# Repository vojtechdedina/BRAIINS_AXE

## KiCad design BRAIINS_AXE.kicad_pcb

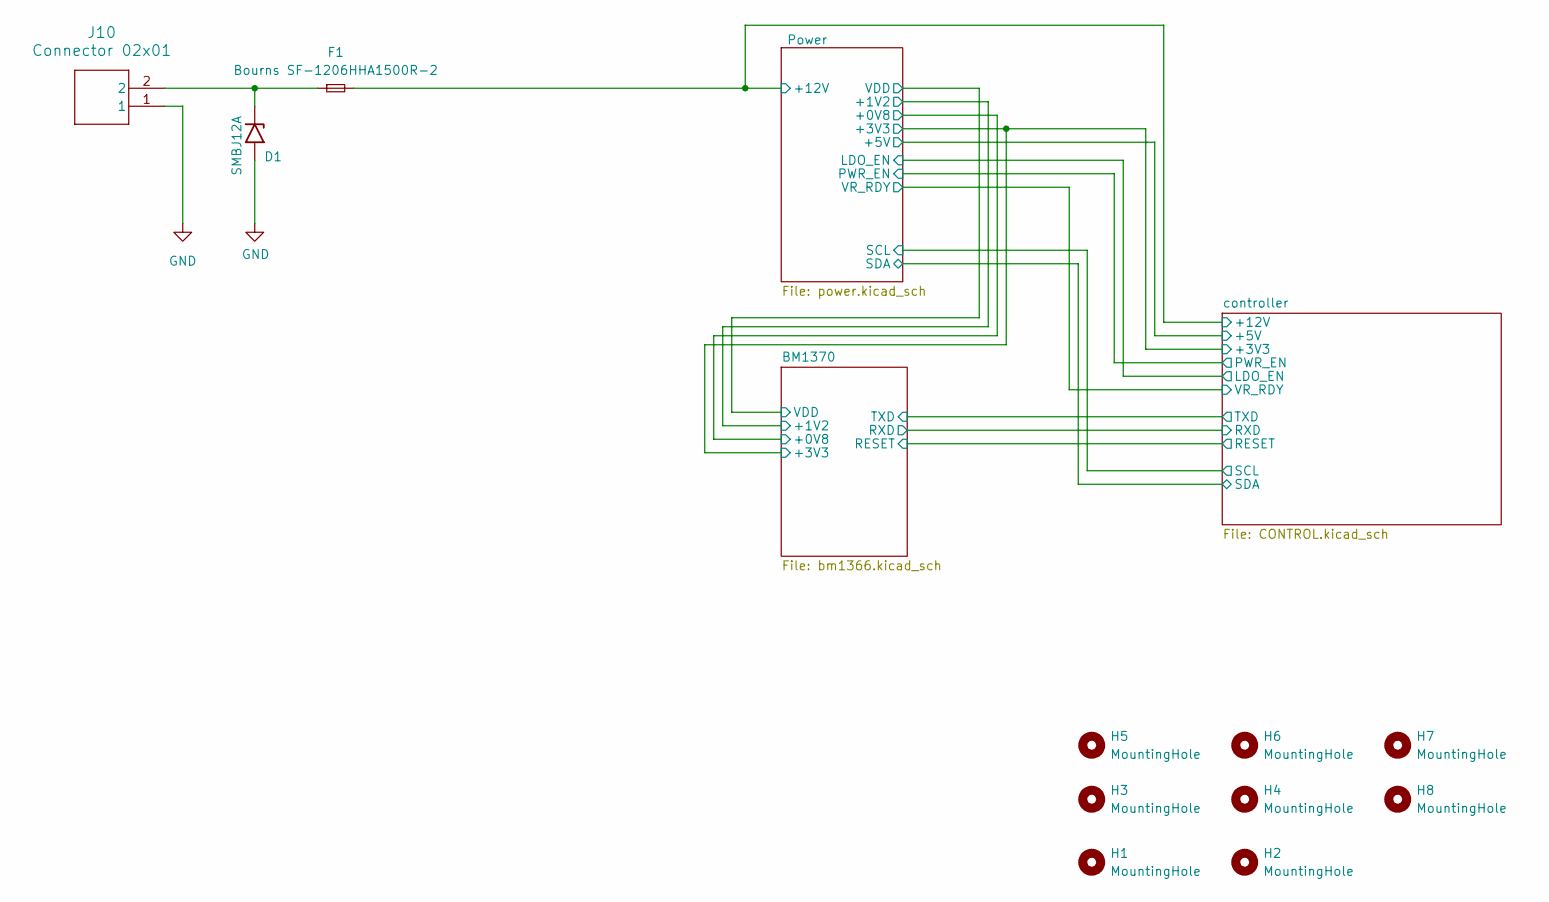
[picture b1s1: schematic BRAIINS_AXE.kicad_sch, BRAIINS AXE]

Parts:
D1: SMBJ12A; D_SMB
F1: Bourns SF-1206HHA1500R-2; Fuse_1210_3225Metric
H1, H2, H3, H4, H5, H6, H7, H8: MountingHole; MountingHole_3.2mm_M3_Pad_Via
J10: Connector 02x01; AMASS_XT60PW-M_1x02_P7.20mm_Horizontal

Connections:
+12V: F1.2; also elsewhere on the board
GND: D1.2 (A2), J10.1; also elsewhere on the board
unnamed: D1.1 (A1), F1.1, J10.2

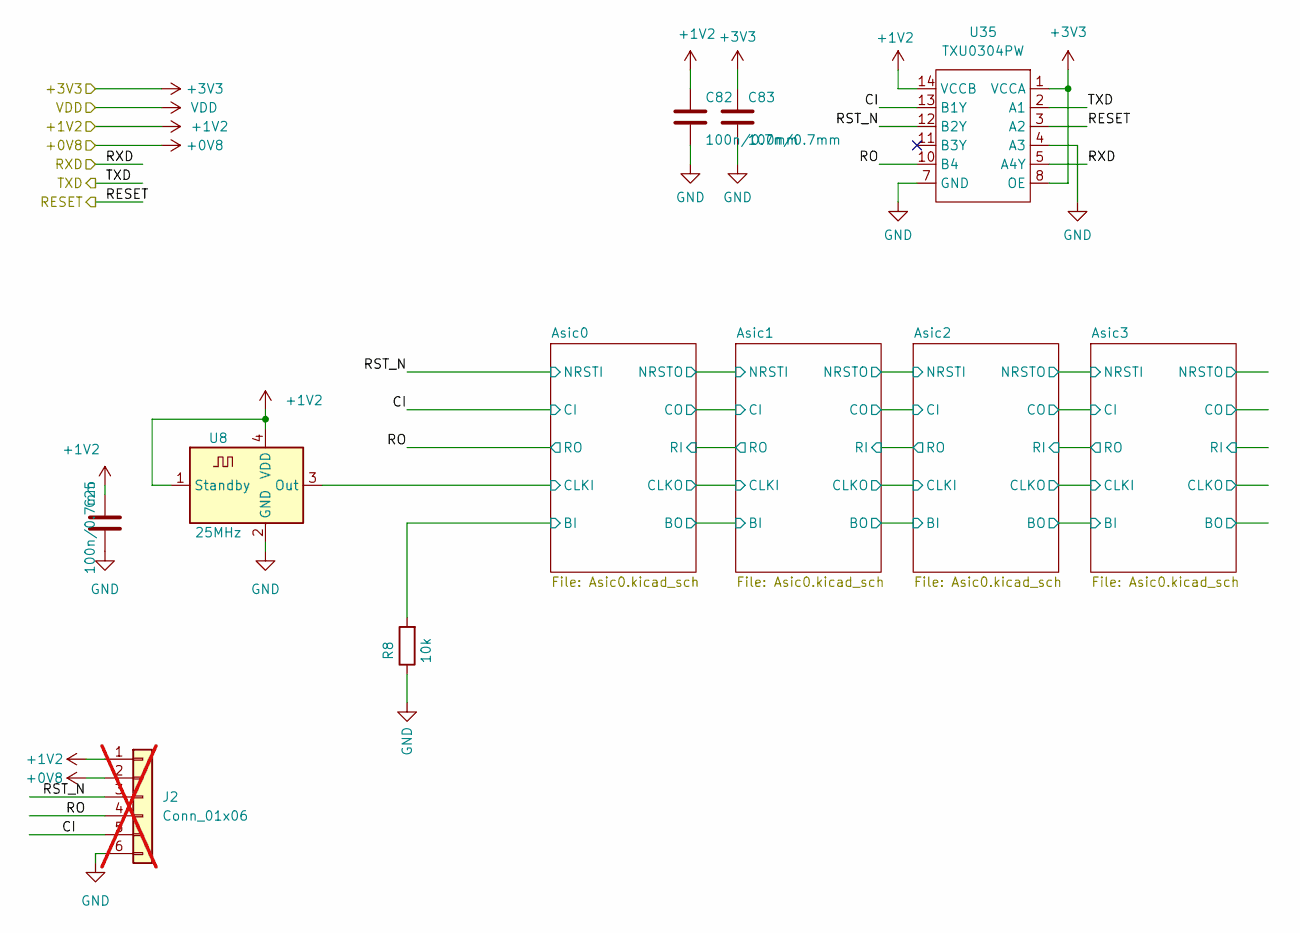
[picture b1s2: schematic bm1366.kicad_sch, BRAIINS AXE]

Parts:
C25, C82, C83: 100n/0.7mm; C_0805_2012Metric
J2: Conn_01x06; PinHeader_1x06_P1.27mm_Vertical; not fitted
R8: 10k; R_0805_2012Metric
U8: 25MHz; Oscillator_SMD_EuroQuartz_XO32-4Pin_3.2x2.5mm
U35: TXU0304PW; TSSOP-14-1EP_4.4x5mm_P0.65mm

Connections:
+0V8: J2.2; also elsewhere on the board
+1V2: C25.1, C82.1, J2.1, U8.1 (Standby), U8.4 (VDD), U35.14 (VCCB); also elsewhere on the board
+3V3: C83.1, U35.1 (VCCA), U35.8 (OE); also elsewhere on the board
/BM1370/Asic0/BI: R8.2; also elsewhere on the board
/BM1370/Asic0/CLKI: U8.3 (Out); also elsewhere on the board
/BM1370/CI: J2.5, U35.13 (B1Y); also elsewhere on the board
/BM1370/RESET: U35.3 (A2); also elsewhere on the board
/BM1370/RO: J2.4, U35.10 (B4); also elsewhere on the board
/BM1370/RST_N: J2.3, U35.12 (B2Y); also elsewhere on the board
/BM1370/RXD: U35.5 (A4Y); also elsewhere on the board
/BM1370/TXD: U35.2 (A1); also elsewhere on the board
GND: C25.2, C82.2, C83.2, J2.6, R8.1, U8.2 (GND), U35.4 (A3), U35.7 (GND); also elsewhere on the board

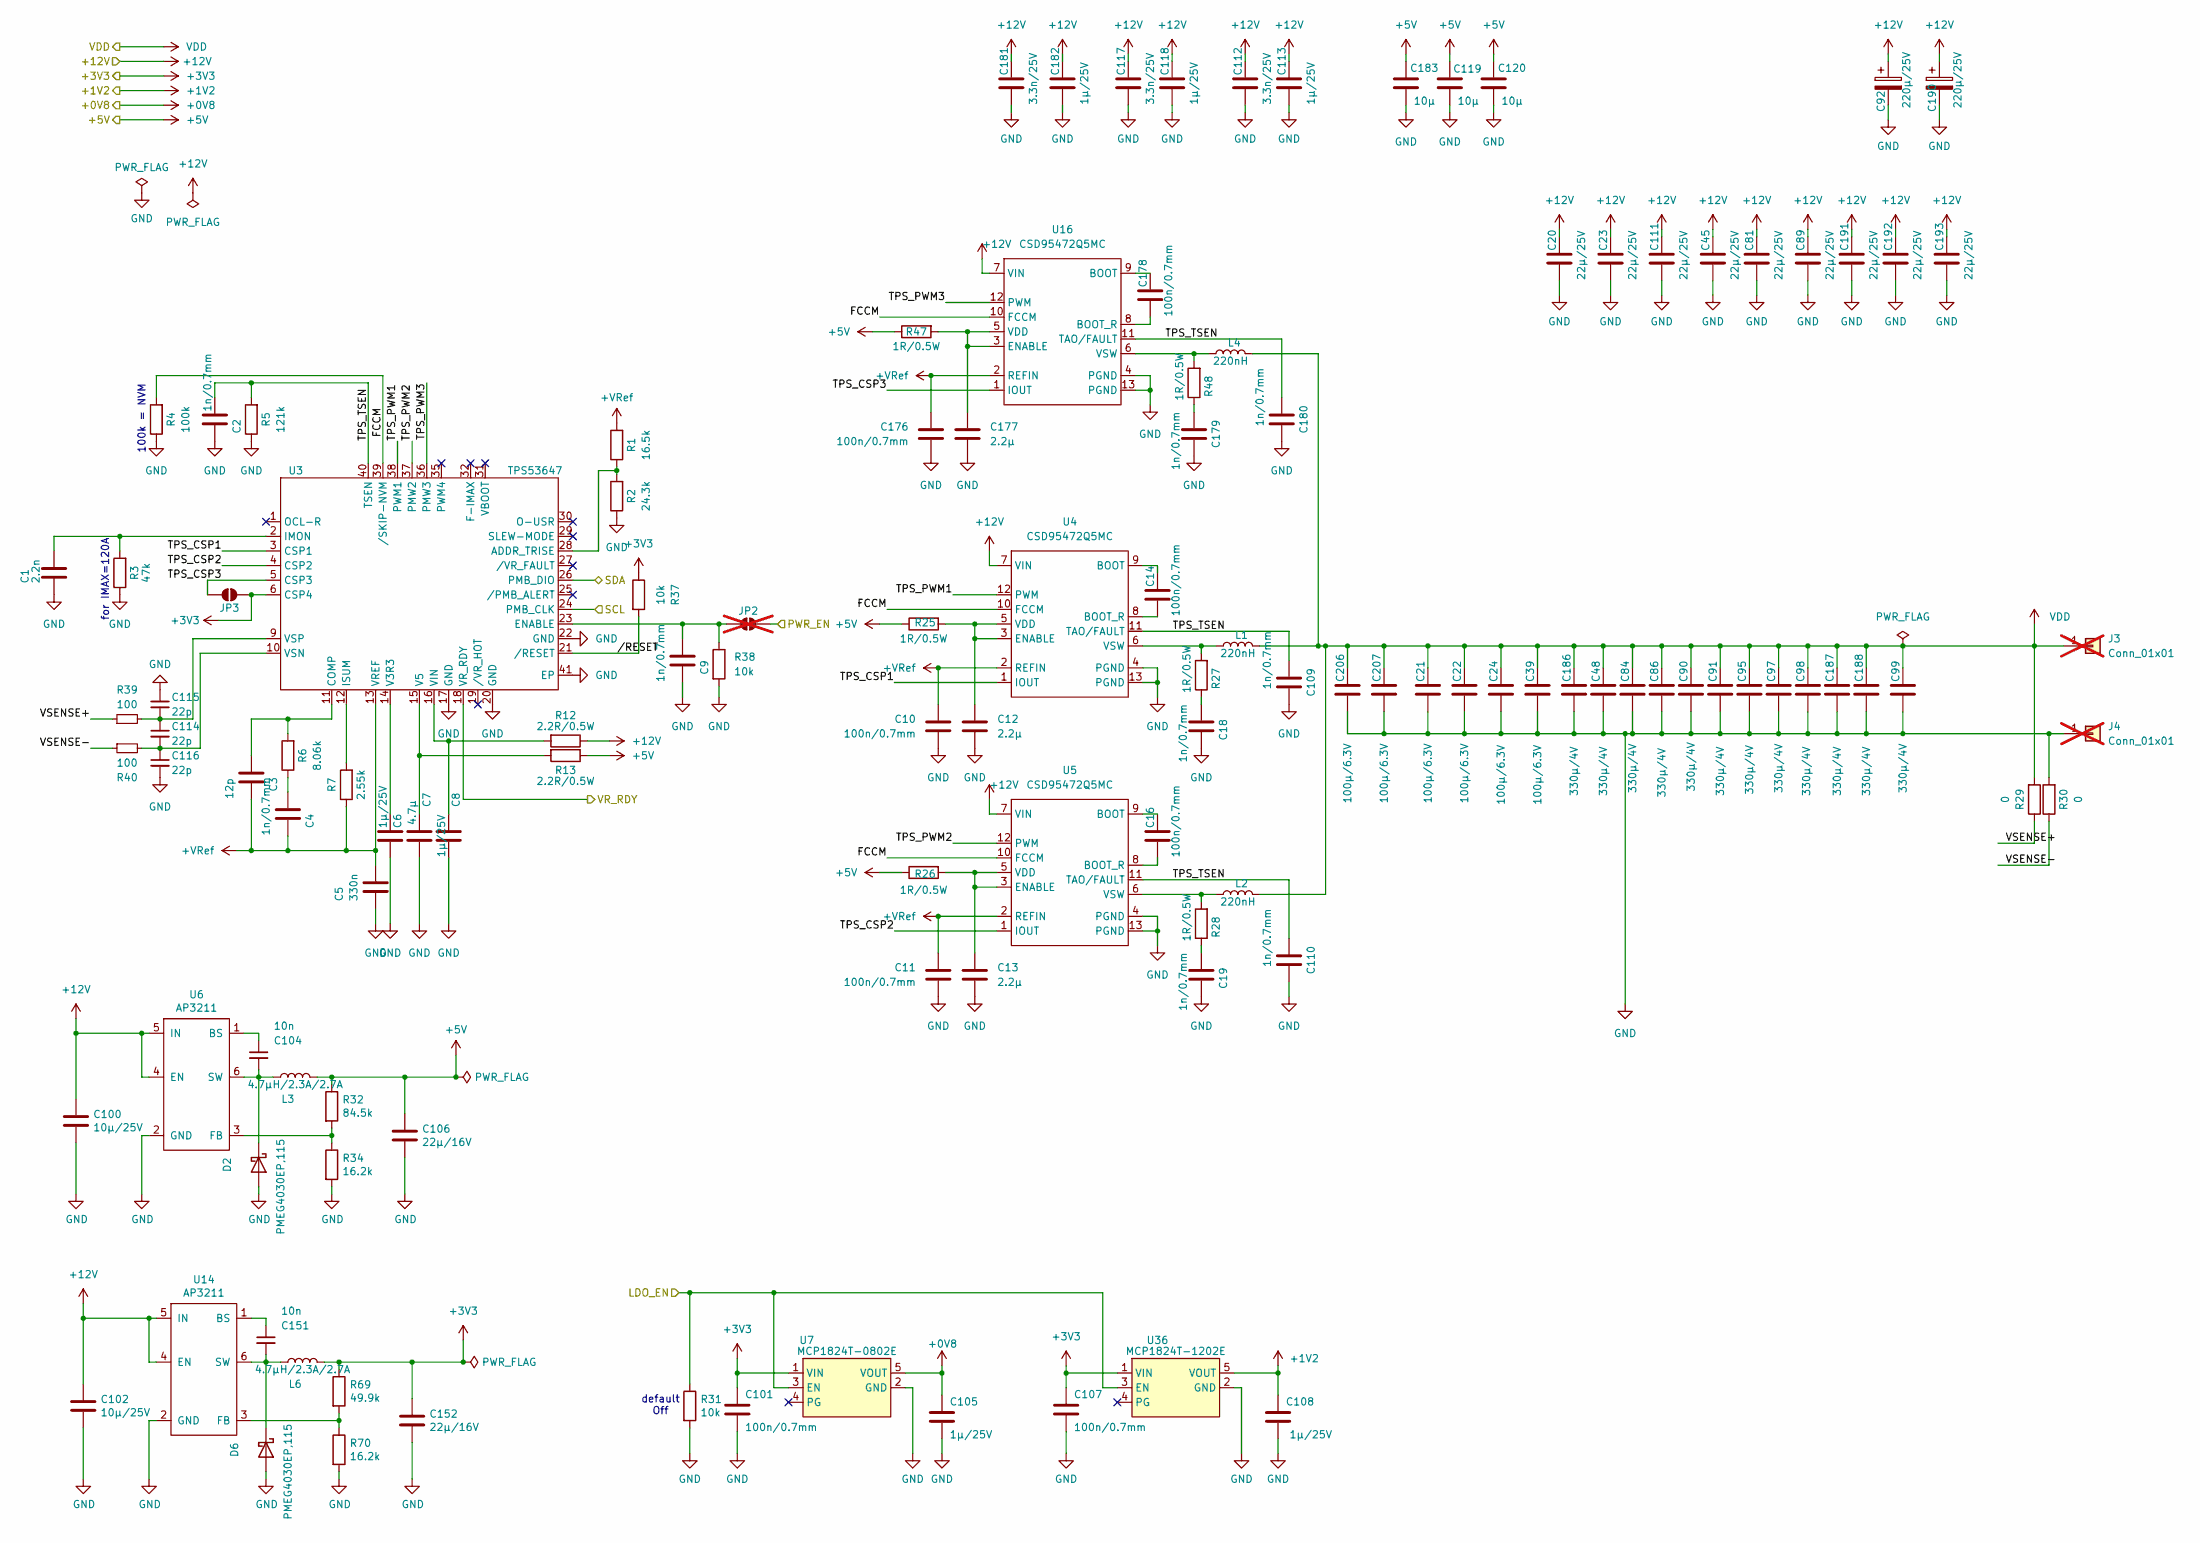
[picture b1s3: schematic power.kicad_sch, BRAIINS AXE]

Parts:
C1: 2.2n; C_0603_1608Metric
C2, C4, C9: 1n/0.7mm; C_0603_1608Metric
C3: 12p; C_0603_1608Metric
C5: 330n; C_0603_1608Metric
C6, C8, C113, C118, C182: 1µ/25V; C_0603_1608Metric
C7: 4.7µ; C_0603_1608Metric
C10, C11, C14, C16, C176, C178: 100n/0.7mm; C_0603_1608Metric
C12, C13, C177: 2.2µ; C_0603_1608Metric
C18, C19, C109, C110, C179, C180: 1n/0.7mm; C_0805_2012Metric
C20, C23, C45, C81, C89, C111, C191, C192, C193: 22µ/25V; C_1210_3225Metric
C21, C22, C24, C39, C206, C207: 100µ/6.3V; C_1210_3225Metric
C48, C84, C86, C90, C91, C95, C97, C98, C99, C186, C187, C188: 330µ/4V; C_1210_3225Metric
C92, C190: 220µ/25V; CP_Elec_8x10
C100, C102: 10µ/25V; C_0805_2012Metric
C101, C107: 100n/0.7mm; C_0805_2012Metric
C104, C151: 10n; C_0805_2012Metric
C105, C108: 1µ/25V; C_0805_2012Metric
C106, C152: 22µ/16V; C_1206_3216Metric
C112, C117, C181: 3.3n/25V; C_0603_1608Metric
C114, C115, C116: 22p; C_0603_1608Metric
C119, C120, C183: 10µ; C_0805_2012Metric
D2, D6: PMEG4030EP,115; D_SOD-128
J3, J4: Conn_01x01; Wuerth_REDCUBE-THR_WP-THRBU_74650194_THR; not fitted
JP2: SolderJumper_2_Open; SolderJumper-2_P1.3mm_Open_RoundedPad1.0x1.5mm; not fitted
JP3: SolderJumper_2_Open; SolderJumper-2_P1.3mm_Open_RoundedPad1.0x1.5mm
L1, L2, L4: 220nH; IFLR-4031GC-01-8x10
L3, L6: 4.7µH/2.3A/2.7A; L_Taiyo-Yuden_NR-50xx
R1: 16.5k; R_0603_1608Metric
R2: 24.3k; R_0603_1608Metric
R3: 47k; R_0603_1608Metric
R4: 100k; R_0603_1608Metric
R5: 121k; R_0603_1608Metric
R6: 8.06k; R_0603_1608Metric
R7: 2.55k; R_0603_1608Metric
R12, R13: 2.2R/0.5W; R_0805_2012Metric
R25, R26, R27, R28, R47, R48: 1R/0.5W; R_0805_2012Metric
R29, R30: 0; R_0805_2012Metric
R31: 10k; R_0805_2012Metric
R32: 84.5k; R_0603_1608Metric
R34, R70: 16.2k; R_0603_1608Metric
R37, R38: 10k; R_0603_1608Metric
R39, R40: 100; R_0603_1608Metric
R69: 49.9k; R_0603_1608Metric
U3: TPS53647; Texas_RHA0040B_VQFN-40-1EP_6x6mm_P0.5mm_EP4.15x4.15mm_Therm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
U4, U5, U16: CSD95472Q5MC; CSD95472-SON-5x6
U6, U14: AP3211; SOT-23-6
U7: MCP1824T-0802E; SOT-23-5
U36: MCP1824T-1202E; SOT-23-5

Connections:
+0V8: C105.1, U7.5 (VOUT); also elsewhere on the board
+1V2: C108.1, U36.5 (VOUT); also elsewhere on the board
+3V3: C101.1, C107.1, C152.1, JP3.2 (B), L6.2, R37.1, R69.1, U3.6 (CSP4), U7.1 (VIN), U36.1 (VIN); also elsewhere on the board
+5V: C106.1, C119.1, C120.1, C183.1, L3.2, R13.1, R25.1, R26.1, R32.1, R47.1
+12V: C20.1, C23.1, C45.1, C81.1, C89.1, C92.1, C100.1, C102.1, C111.1, C112.1, C113.1, C117.1, C118.1, C181.1, C182.1, C190.1, C191.1, C192.1, C193.1, R12.1, U4.7 (VIN), U5.7 (VIN), U6.4 (EN), U6.5 (IN), U14.4 (EN), U14.5 (IN), U16.7 (VIN); also elsewhere on the board
+VRef: C3.2, C4.2, C5.1, C10.1, C11.1, C176.1, R1.2, R7.1, U3.13 (VREF), U4.2 (REFIN), U5.2 (REFIN), U16.2 (REFIN)
/Power/FCCM: R4.2, U3.39 (/SKIP-NVM), U4.10 (FCCM), U5.10 (FCCM), U16.10 (FCCM)
/Power/LDO_EN: R31.1, U7.3 (EN), U36.3 (EN); also elsewhere on the board
/Power/PWR_EN: JP2.2 (B); also elsewhere on the board
/Power/TPS_CSP1: U3.3 (CSP1), U4.1 (IOUT)
/Power/TPS_CSP2: U3.4 (CSP2), U5.1 (IOUT)
/Power/TPS_CSP3: JP3.1 (A), U3.5 (CSP3), U16.1 (IOUT)
/Power/TPS_PWM1: U3.38 (PWM1), U4.12 (PWM)
/Power/TPS_PWM2: U3.37 (PMW2), U5.12 (PWM)
/Power/TPS_PWM3: U3.36 (PMW3), U16.12 (PWM)
/Power/TPS_TSEN: C2.1, C109.1, C110.1, C180.1, R5.2, U3.40 (TSEN), U4.11 (TAO/FAULT), U5.11 (TAO/FAULT), U16.11 (TAO/FAULT)
/Power/VR_RDY: U3.18 (VR_RDY); also elsewhere on the board
/Power/VSENSE+: R29.1, R39.1
/Power/VSENSE-: R30.1, R40.1
/Power//RESET: R37.2, U3.21 (/RESET)
/controller/SCL: U3.24 (PMB_CLK); also elsewhere on the board
/controller/SDA: U3.26 (PMB_DIO); also elsewhere on the board
GND: C1.2, C2.2, C5.2, C6.2, C7.1, C8.1, C9.2, C10.2, C11.2, C12.2, C13.2, C18.2, C19.2, C20.2, C21.2, C22.2, C23.2, C24.2, C39.2, C45.2, C48.2, C81.2, C84.2, C86.2, C89.2, C90.2, C91.2, C92.2, C95.2, C97.2, C98.2, C99.2, C100.2, C101.2, C102.2, C105.2, C106.2, C107.2, C108.2, C109.2, C110.2, C111.2, C112.2, C113.2, C115.1, C116.2, C117.2, C118.2, C119.2, C120.2, C152.2, C176.2, C177.2, C179.2, C180.2, C181.2, C182.2, C183.2, C186.2, C187.2, C188.2, C190.2, C191.2, C192.2, C193.2, C206.2, C207.2, D2.2 (A), D6.2 (A), J4.1, R2.1, R3.1, R4.1, R5.1, R30.2, R31.2, R34.2, R38.2, R70.2, U3.17 (GND), U3.20 (GND), U3.22 (GND), U3.41 (EP), U4.4 (PGND), U4.13 (PGND), U5.4 (PGND), U5.13 (PGND), U6.2 (GND), U7.2 (GND), U14.2 (GND), U16.4 (PGND), U16.13 (PGND), U36.2 (GND); also elsewhere on the board
unnamed: C4.1, R6.1
unnamed: C18.1, R27.1
unnamed: C19.1, R28.1
unnamed: C179.1, R48.1
unnamed: C104.2, D2.1 (K), L3.1, U6.6 (SW)
unnamed: C151.2, D6.1 (K), L6.1, U14.6 (SW)
unnamed: C9.1, JP2.1 (A), R38.1, U3.23 (ENABLE)
unnamed: R1.1, R2.2, U3.28 (ADDR_TRISE)
unnamed: C3.1, R6.2, U3.11 (COMP)
unnamed: C1.1, R3.2, U3.2 (IMON)
unnamed: R7.2, U3.12 (ISUM)
unnamed: C6.1, U3.14 (V3R3)
unnamed: C7.2, R13.2, U3.15 (V5)
unnamed: C8.2, R12.2, U3.16 (VIN)
unnamed: C114.2, C116.1, R40.2, U3.10 (VSN)
unnamed: C114.1, C115.2, R39.2, U3.9 (VSP)
unnamed: C14.1, U4.9 (BOOT)
unnamed: C14.2, U4.8 (BOOT_R)
unnamed: C12.1, R25.2, U4.3 (ENABLE), U4.5 (VDD)
unnamed: L1.1, R27.2, U4.6 (VSW)
unnamed: C16.1, U5.9 (BOOT)
unnamed: C16.2, U5.8 (BOOT_R)
unnamed: C13.1, R26.2, U5.3 (ENABLE), U5.5 (VDD)
unnamed: L2.1, R28.2, U5.6 (VSW)
unnamed: C104.1, U6.1 (BS)
unnamed: R32.2, R34.1, U6.3 (FB)
unnamed: C151.1, U14.1 (BS)
unnamed: R69.2, R70.1, U14.3 (FB)
unnamed: C178.1, U16.9 (BOOT)
unnamed: C178.2, U16.8 (BOOT_R)
unnamed: C177.1, R47.2, U16.3 (ENABLE), U16.5 (VDD)
unnamed: L4.1, R48.2, U16.6 (VSW)
VDD: C21.1, C22.1, C24.1, C39.1, C48.1, C84.1, C86.1, C90.1, C91.1, C95.1, C97.1, C98.1, C99.1, C186.1, C187.1, C188.1, C206.1, C207.1, J3.1, L1.2, L2.2, L4.2, R29.2; also elsewhere on the board

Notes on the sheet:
default Off
for IMAX=120A
100k = NVM

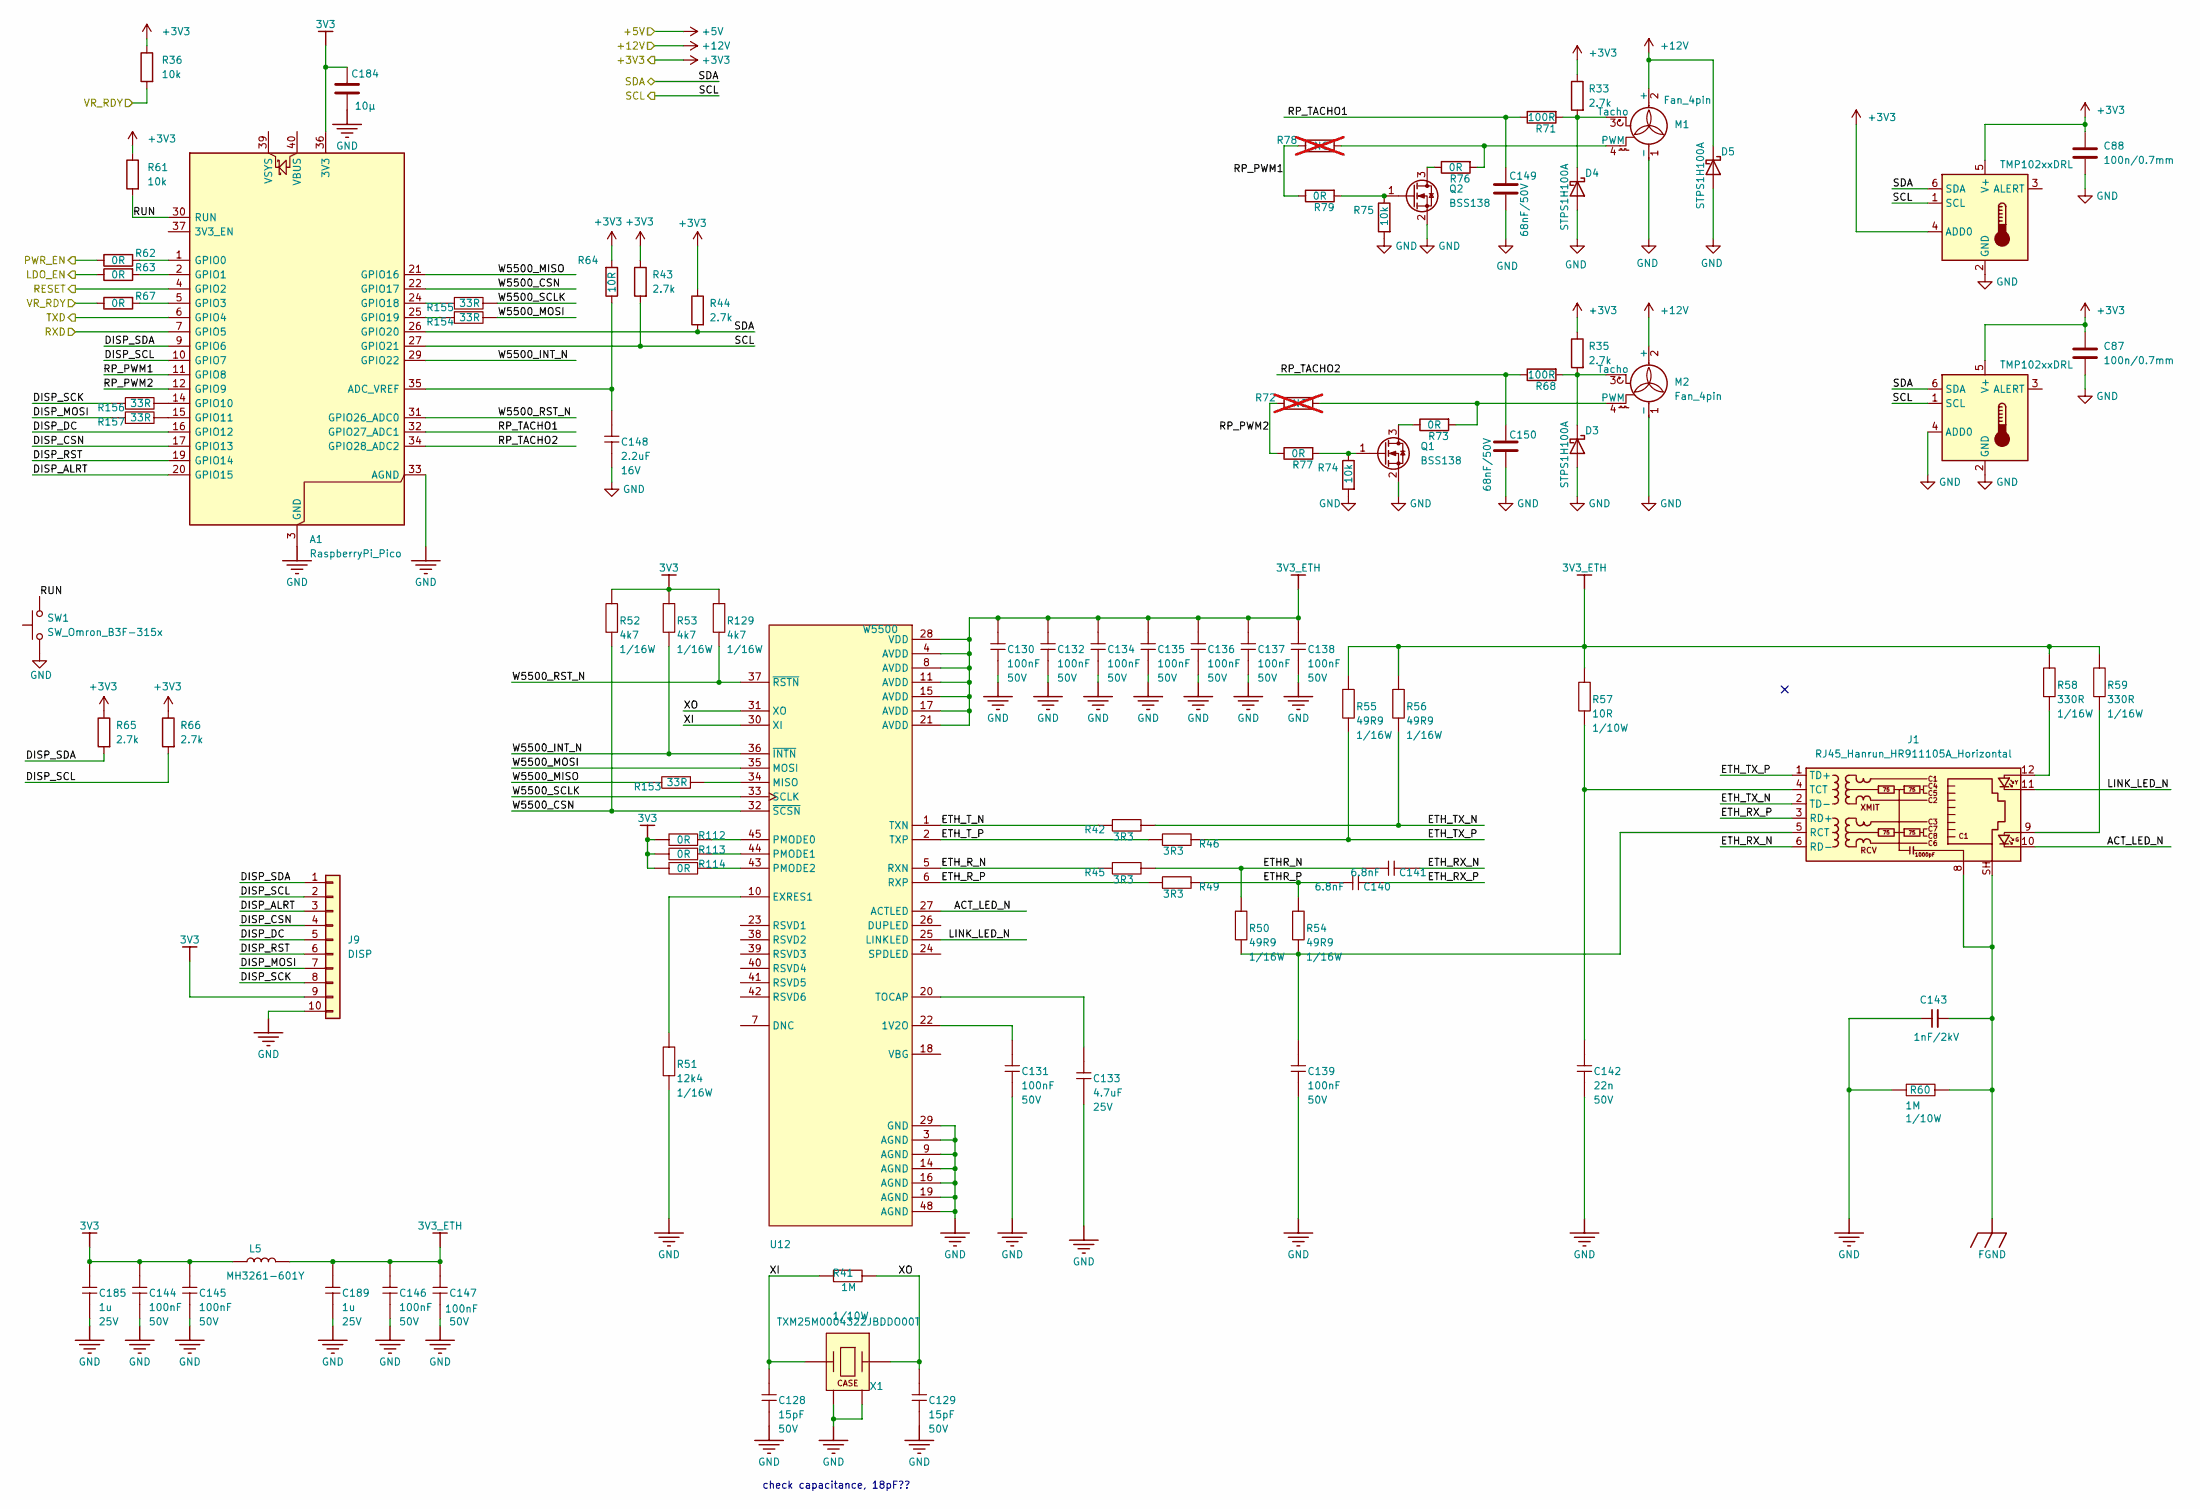
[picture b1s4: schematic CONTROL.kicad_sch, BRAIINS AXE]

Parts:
A1: RaspberryPi_Pico; RaspberryPi_Pico_Common_Unspecified
C87, C88: 100n/0.7mm; C_0603_1608Metric
C128, C129: 15pF; C_0603_1608Metric; VOLTAGE_RATING 50V; TOLERANCE 1%; PART_TYPE Capacitor
C130, C131, C132, C134, C135, C136, C137, C138, C139, C144, C145, C146, C147: 100nF; C_0603_1608Metric; VOLTAGE_RATING 50V; TOLERANCE 10%; PART_TYPE Capacitor
C133: 4.7uF; C_0603_1608Metric; VOLTAGE_RATING 25V; TOLERANCE 10%; PART_TYPE Capacitor
C140, C141: 6.8nF; C_0603_1608Metric; VOLTAGE_RATING 50V; TOLERANCE 10%; PART_TYPE Capacitor
C142: 22n; C_0603_1608Metric; VOLTAGE_RATING 50V; TOLERANCE 10%; PART_TYPE Capacitor
C143: 1nF/2kV; C_1206_3216Metric
C148: 2.2uF; C_0603_1608Metric; VOLTAGE_RATING 16V; TOLERANCE 10%; PART_TYPE Capacitor
C149, C150: 68nF/50V; C_0603_1608Metric
C184: 10µ; C_0805_2012Metric
C185, C189: 1u; C_0603_1608Metric; VOLTAGE_RATING 25V; TOLERANCE 10%; PART_TYPE Capacitor
D3, D4, D5: STPS1H100A; D_SMA
J1: RJ45_Hanrun_HR911105A_Horizontal
J9: DISP; PinHeader_1x10_P2.54mm_Vertical
L5: MH3261-601Y; L_1206_3216Metric; PART_TYPE Filter
M1, M2: Fan_4pin; FanPinHeader_1x04_P2.54mm_Vertical
Q1, Q2: BSS138; SOT-23
R33, R35, R43, R44, R65, R66: 2.7k; R_0603_1608Metric
R36, R61, R74, R75: 10k; R_0603_1608Metric
R41, R60: 1M; R_0603_1608Metric; TOLERANCE 1%; PART_TYPE Resistor
R42, R45, R46, R49: 3R3; R_0603_1608Metric; TOLERANCE 1%; PART_TYPE Resistor
R50, R54, R55, R56: 49R9; R_0603_1608Metric; TOLERANCE 1%; PART_TYPE Resistor
R51: 12k4; R_0603_1608Metric; TOLERANCE 1%; PART_TYPE Resistor
R52, R53, R129: 4k7; R_0603_1608Metric; TOLERANCE 1%; PART_TYPE Resistor
R57: 10R; R_0603_1608Metric; TOLERANCE 1%; PART_TYPE Resistor
R58, R59: 330R; R_0603_1608Metric; TOLERANCE 1%; PART_TYPE Resistor
R62, R63, R67, R73, R76, R77, R79: 0R; R_0603_1608Metric
R64: 10R; R_0603_1608Metric
R68, R71: 100R; R_0603_1608Metric
R72, R78: NC; R_0603_1608Metric; not fitted
R112, R113, R114: 0R; R_0603_1608Metric; TOLERANCE 1%; PART_TYPE Resistor
R153, R154, R155, R156, R157: 33R; R_0603_1608Metric; TOLERANCE 1%; PART_TYPE Resistor
SW1: SW_Omron_B3F-315x; SW_SPST_Omron_B3F-315x_Angled
U1, U13: TMP102xxDRL; SOT-563
U12: W5500; LQFP-48_7x7mm_P0.5mm; PART_TYPE IC; LCSC C32843
X1: TXM25M0004322JBDDO00T; Crystal_SMD_3225-4Pin_3.2x2.5mm; PART_TYPE Crystal; LCSC C362473

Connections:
3V3: A1.36 (3V3), C144.1, C145.1, C184.1, C185.1, J9.9, L5.1, R52.2, R53.2, R112.2, R113.2, R114.2, R129.2
3V3_ETH: C130.1, C132.1, C134.1, C135.1, C136.1, C137.1, C138.1, C146.1, C147.1, C189.1, L5.2, R55.2, R56.2, R57.2, R58.2, R59.2, U12.4 (AVDD), U12.8 (AVDD), U12.11 (AVDD), U12.15 (AVDD), U12.17 (AVDD), U12.21 (AVDD), U12.28 (VDD)
+3V3: C87.1, C88.1, R33.1, R35.1, R36.1, R43.1, R44.1, R61.1, R64.2, R65.1, R66.1, U1.5 (V+), U13.4 (ADD0), U13.5 (V+); also elsewhere on the board
+12V: D5.1 (K), M1.2 (+), M2.2 (+); also elsewhere on the board
/BM1370/RESET: A1.4 (GPIO2); also elsewhere on the board
/BM1370/RXD: A1.7 (GPIO5); also elsewhere on the board
/BM1370/TXD: A1.6 (GPIO4); also elsewhere on the board
/Power/LDO_EN: R63.1; also elsewhere on the board
/Power/PWR_EN: R62.1; also elsewhere on the board
/Power/VR_RDY: R36.2, R67.1; also elsewhere on the board
/controller/ACT_LED_N: J1.10, U12.27 (ACTLED)
/controller/DISP_ALRT: A1.20 (GPIO15), J9.3
/controller/DISP_CSN: A1.17 (GPIO13), J9.4
/controller/DISP_DC: A1.16 (GPIO12), J9.5
/controller/DISP_MOSI: J9.7, R157.1
/controller/DISP_RST: A1.19 (GPIO14), J9.6
/controller/DISP_SCK: J9.8, R156.1
/controller/DISP_SCL: A1.10 (GPIO7), J9.2, R66.2
/controller/DISP_SDA: A1.9 (GPIO6), J9.1, R65.2
/controller/ETHR_N: C141.1, R45.2, R50.2
/controller/ETHR_P: C140.1, R49.2, R54.2
/controller/ETH_RX_N: C141.2, J1.6 (RD-)
/controller/ETH_RX_P: C140.2, J1.3 (RD+)
/controller/ETH_R_N: R45.1, U12.5 (RXN)
/controller/ETH_R_P: R49.1, U12.6 (RXP)
/controller/ETH_TX_N: J1.2 (TD-), R42.2, R56.1
/controller/ETH_TX_P: J1.1 (TD+), R46.2, R55.1
/controller/ETH_T_N: R42.1, U12.1 (TXN)
/controller/ETH_T_P: R46.1, U12.2 (TXP)
/controller/LINK_LED_N: J1.11, U12.25 (LINKLED)
/controller/RP_PWM1: A1.11 (GPIO8), R78.1, R79.1
/controller/RP_PWM2: A1.12 (GPIO9), R72.1, R77.1
/controller/RP_TACHO1: A1.32 (GPIO27_ADC1), C149.1, R71.1
/controller/RP_TACHO2: A1.34 (GPIO28_ADC2), C150.1, R68.1
/controller/RUN: A1.30 (RUN), R61.2, SW1.2
/controller/SCL: A1.27 (GPIO21), R43.2, U1.1 (SCL), U13.1 (SCL); also elsewhere on the board
/controller/SDA: A1.26 (GPIO20), R44.2, U1.6 (SDA), U13.6 (SDA); also elsewhere on the board
/controller/W5500_CSN: A1.22 (GPIO17), R52.1, U12.32 (~SCSN)
/controller/W5500_INT_N: A1.29 (GPIO22), R53.1, U12.36 (~INTN)
/controller/W5500_MISO: A1.21 (GPIO16), R153.1
/controller/W5500_MOSI: R154.2, U12.35 (MOSI)
/controller/W5500_RST_N: A1.31 (GPIO26_ADC0), R129.1, U12.37 (~RSTN)
/controller/W5500_SCLK: R155.2, U12.33 (SCLK)
/controller/XI: C128.1, R41.1, U12.30 (XI), X1.1 (X1)
/controller/XO: C129.1, R41.2, U12.31 (XO), X1.3 (X2)
FGND: C143.2, J1.8, J1.SH, R60.2
GND: A1.3 (GND), A1.8 (GND), A1.13 (GND), A1.18 (GND), A1.23 (GND), A1.28 (GND), A1.33 (AGND), A1.38 (GND), C87.2, C88.2, C128.2, C129.2, C130.2, C131.2, C132.2, C133.2, C134.2, C135.2, C136.2, C137.2, C138.2, C139.2, C142.2, C143.1, C144.2, C145.2, C146.2, C147.2, C148.2, C149.2, C150.2, C184.2, C185.2, C189.2, D3.2 (A), D4.2 (A), D5.2 (A), J9.10, M1.1 (-), M2.1 (-), Q1.2 (S), Q2.2 (S), R51.1, R60.1, R74.2, R75.2, SW1.1, U1.2 (GND), U1.4 (ADD0), U12.3 (AGND), U12.9 (AGND), U12.14 (AGND), U12.16 (AGND), U12.19 (AGND), U12.29 (GND), U12.48 (AGND), U13.2 (GND), X1.2 (CASE), X1.4 (CASE); also elsewhere on the board
unnamed: A1.35 (ADC_VREF), C148.1, R64.1
unnamed: A1.1 (GPIO0), R62.2
unnamed: A1.2 (GPIO1), R63.2
unnamed: A1.5 (GPIO3), R67.2
unnamed: A1.14 (GPIO10), R156.2
unnamed: A1.15 (GPIO11), R157.2
unnamed: A1.24 (GPIO18), R155.1
unnamed: A1.25 (GPIO19), R154.1
unnamed: D3.1 (K), M2.3 (Tacho), R35.2, R68.2
unnamed: D4.1 (K), M1.3 (Tacho), R33.2, R71.2
unnamed: J1.9, R59.1
unnamed: J1.12, R58.1
unnamed: C139.1, J1.5 (RCT), R50.1, R54.1
unnamed: C142.1, J1.4 (TCT), R57.1
unnamed: M1.4 (PWM), R76.2, R78.2
unnamed: M2.4 (PWM), R72.2, R73.2
unnamed: Q1.3 (D), R73.1
unnamed: Q1.1 (G), R74.1, R77.2
unnamed: Q2.3 (D), R76.1
unnamed: Q2.1 (G), R75.1, R79.2
unnamed: C131.1, U12.22 (1V2O)
unnamed: R51.2, U12.10 (EXRES1)
unnamed: R153.2, U12.34 (MISO)
unnamed: R112.1, U12.45 (PMODE0)
unnamed: R113.1, U12.44 (PMODE1)
unnamed: R114.1, U12.43 (PMODE2)
unnamed: C133.1, U12.20 (TOCAP)

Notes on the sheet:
check capacitance, 18pF??

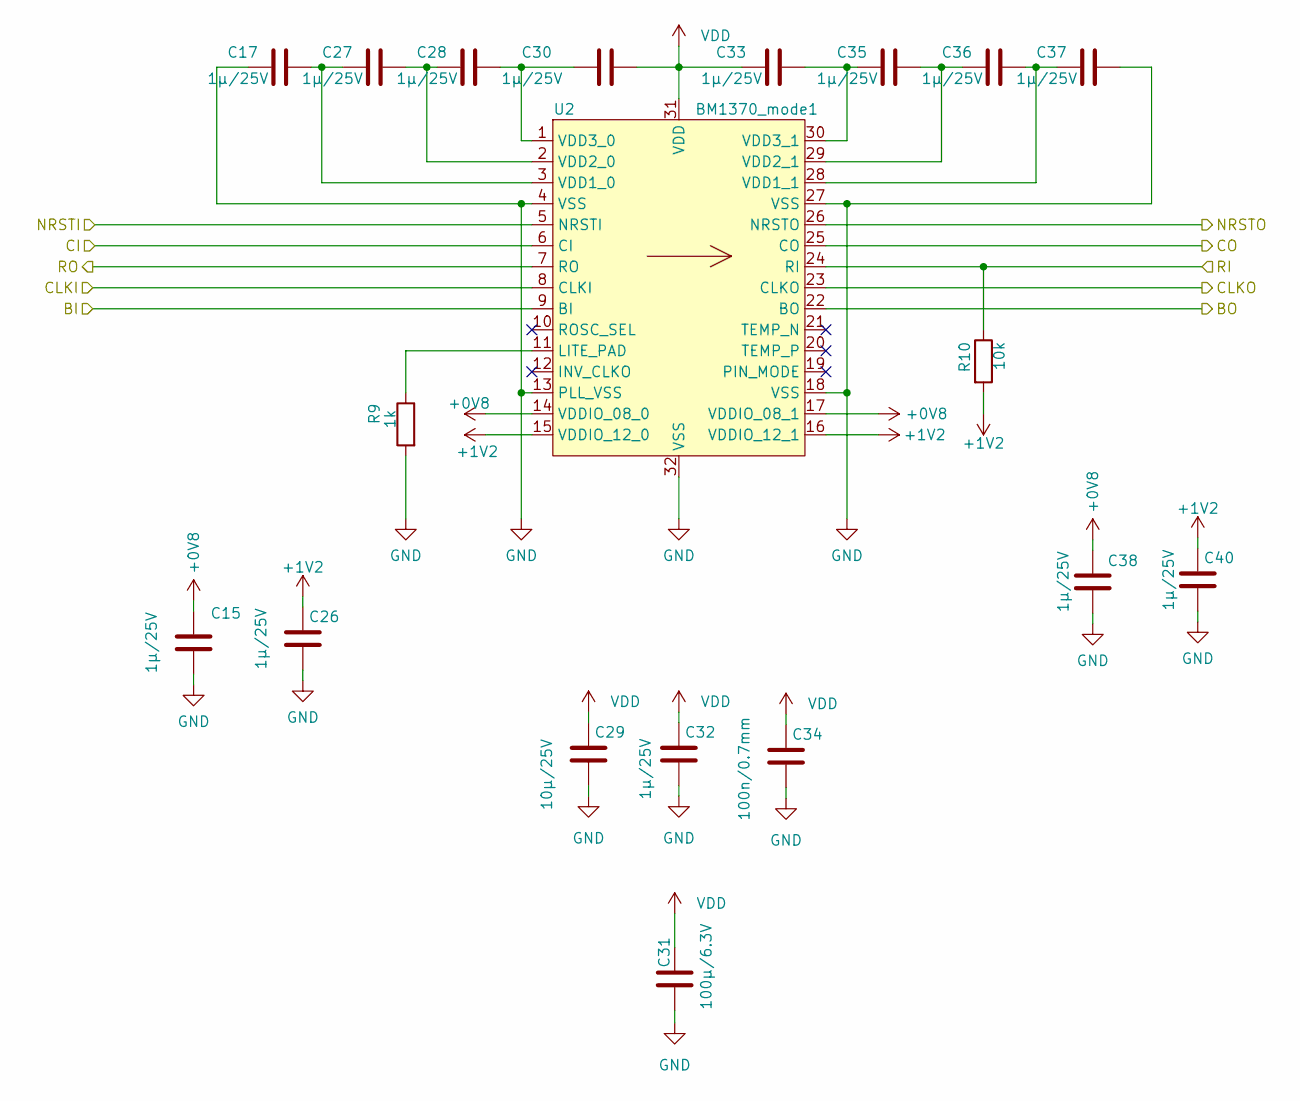
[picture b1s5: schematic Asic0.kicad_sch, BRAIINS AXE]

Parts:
C15, C17, C26, C27, C28, C30, C32, C33, C35, C36, C37, C38, C40: 1µ/25V; C_0805_2012Metric
C29: 10µ/25V; C_0805_2012Metric
C31: 100µ/6.3V; C_1210_3225Metric
C34: 100n/0.7mm; C_0805_2012Metric
R9: 1k; R_0805_2012Metric
R10: 10k; R_0805_2012Metric
U2: BM1370_mode1; BM1370

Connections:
+0V8: C15.2, C38.2, U2.14 (VDDIO_08_0), U2.17 (VDDIO_08_1); also elsewhere on the board
+1V2: C26.1, C40.1, R10.2, U2.15 (VDDIO_12_0), U2.16 (VDDIO_12_1); also elsewhere on the board
/BM1370/Asic0/BI: U2.9 (BI); also elsewhere on the board
/BM1370/Asic0/BO: U2.22 (BO); also elsewhere on the board
/BM1370/Asic0/CLKI: U2.8 (CLKI); also elsewhere on the board
/BM1370/Asic0/CLKO: U2.23 (CLKO); also elsewhere on the board
/BM1370/Asic0/CO: U2.25 (CO); also elsewhere on the board
/BM1370/Asic0/NRSTO: U2.26 (NRSTO); also elsewhere on the board
/BM1370/Asic0/RI: R10.1, U2.24 (RI); also elsewhere on the board
/BM1370/CI: U2.6 (CI); also elsewhere on the board
/BM1370/RO: U2.7 (RO); also elsewhere on the board
/BM1370/RST_N: U2.5 (NRSTI); also elsewhere on the board
GND: C15.1, C17.1, C26.2, C29.2, C31.2, C32.2, C34.2, C37.2, C38.1, C40.2, R9.2, U2.4 (VSS), U2.13 (PLL_VSS), U2.18 (VSS), U2.27 (VSS), U2.32 (VSS); also elsewhere on the board
unnamed: R9.1, U2.11 (LITE_PAD)
unnamed: C17.2, C27.1, U2.3 (VDD1_0)
unnamed: C36.2, C37.1, U2.28 (VDD1_1)
unnamed: C27.2, C28.1, U2.2 (VDD2_0)
unnamed: C35.2, C36.1, U2.29 (VDD2_1)
unnamed: C28.2, C30.1, U2.1 (VDD3_0)
unnamed: C33.2, C35.1, U2.30 (VDD3_1)
VDD: C29.1, C30.2, C31.1, C32.1, C33.1, C34.1, U2.31 (VDD); also elsewhere on the board

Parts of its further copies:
C41, C42, C43, C44, C46, C49, C51, C52, C54, C55, C56, C57, C58, C59, C60, C61, C62, C63, C65, C67, C68, C70, C71, C72, C73, C74, C75, C76, C77, C78, C79, C85, C94, C121, C123, C124, C125, C126, C127: 1µ/25V; C_0805_2012Metric
C47, C64, C80: 10µ/25V; C_0805_2012Metric
C50, C66, C93: 100µ/6.3V; C_1210_3225Metric
C53, C69, C122: 100n/0.7mm; C_0805_2012Metric
R11, R15, R17: 1k; R_0805_2012Metric
R14, R16, R18: 10k; R_0805_2012Metric
U9, U10, U11: BM1370_mode1; BM1370

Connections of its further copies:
+0V8: C41.2, C57.2, C59.2, C73.2, C75.2, C126.2, U9.14 (VDDIO_08_0), U9.17 (VDDIO_08_1), U10.14 (VDDIO_08_0), U10.17 (VDDIO_08_1), U11.14 (VDDIO_08_0), U11.17 (VDDIO_08_1); also elsewhere on the board
+1V2: C43.1, C58.1, C61.1, C74.1, C77.1, C127.1, R14.2, R16.2, R18.2, U9.15 (VDDIO_12_0), U9.16 (VDDIO_12_1), U10.15 (VDDIO_12_0), U10.16 (VDDIO_12_1), U11.15 (VDDIO_12_0), U11.16 (VDDIO_12_1); also elsewhere on the board
/BM1370/Asic0/BO: U9.9 (BI); also elsewhere on the board
/BM1370/Asic0/CLKO: U9.8 (CLKI); also elsewhere on the board
/BM1370/Asic0/CO: U9.6 (CI); also elsewhere on the board
/BM1370/Asic0/NRSTO: U9.5 (NRSTI); also elsewhere on the board
/BM1370/Asic0/RI: U9.7 (RO); also elsewhere on the board
/BM1370/Asic1/BO: U9.22 (BO), U10.9 (BI)
/BM1370/Asic1/CLKO: U9.23 (CLKO), U10.8 (CLKI)
/BM1370/Asic1/CO: U9.25 (CO), U10.6 (CI)
/BM1370/Asic1/NRSTO: U9.26 (NRSTO), U10.5 (NRSTI)
/BM1370/Asic1/RI: R14.1, U9.24 (RI), U10.7 (RO)
/BM1370/Asic2/BO: U10.22 (BO), U11.9 (BI)
/BM1370/Asic2/CLKO: U10.23 (CLKO), U11.8 (CLKI)
/BM1370/Asic2/CO: U10.25 (CO), U11.6 (CI)
/BM1370/Asic2/NRSTO: U10.26 (NRSTO), U11.5 (NRSTI)
/BM1370/Asic2/RI: R16.1, U10.24 (RI), U11.7 (RO)
/BM1370/Asic3/BO: U11.22 (BO)
/BM1370/Asic3/CLKO: U11.23 (CLKO)
/BM1370/Asic3/CO: U11.25 (CO)
/BM1370/Asic3/NRSTO: U11.26 (NRSTO)
/BM1370/Asic3/RI: R18.1, U11.24 (RI)
GND: C41.1, C42.1, C43.2, C47.2, C50.2, C51.2, C53.2, C56.2, C57.1, C58.2, C59.1, C60.1, C61.2, C64.2, C66.2, C67.2, C69.2, C72.2, C73.1, C74.2, C75.1, C76.1, C77.2, C80.2, C93.2, C94.2, C122.2, C125.2, C126.1, C127.2, R11.2, R15.2, R17.2, U9.4 (VSS), U9.13 (PLL_VSS), U9.18 (VSS), U9.27 (VSS), U9.32 (VSS), U10.4 (VSS), U10.13 (PLL_VSS), U10.18 (VSS), U10.27 (VSS), U10.32 (VSS), U11.4 (VSS), U11.13 (PLL_VSS), U11.18 (VSS), U11.27 (VSS), U11.32 (VSS); also elsewhere on the board
unnamed: R11.1, U9.11 (LITE_PAD)
unnamed: C42.2, C44.1, U9.3 (VDD1_0)
unnamed: C55.2, C56.1, U9.28 (VDD1_1)
unnamed: C44.2, C46.1, U9.2 (VDD2_0)
unnamed: C54.2, C55.1, U9.29 (VDD2_1)
unnamed: C46.2, C49.1, U9.1 (VDD3_0)
unnamed: C52.2, C54.1, U9.30 (VDD3_1)
unnamed: R15.1, U10.11 (LITE_PAD)
unnamed: C60.2, C62.1, U10.3 (VDD1_0)
unnamed: C71.2, C72.1, U10.28 (VDD1_1)
unnamed: C62.2, C63.1, U10.2 (VDD2_0)
unnamed: C70.2, C71.1, U10.29 (VDD2_1)
unnamed: C63.2, C65.1, U10.1 (VDD3_0)
unnamed: C68.2, C70.1, U10.30 (VDD3_1)
unnamed: R17.1, U11.11 (LITE_PAD)
unnamed: C76.2, C78.1, U11.3 (VDD1_0)
unnamed: C124.2, C125.1, U11.28 (VDD1_1)
unnamed: C78.2, C79.1, U11.2 (VDD2_0)
unnamed: C123.2, C124.1, U11.29 (VDD2_1)
unnamed: C79.2, C85.1, U11.1 (VDD3_0)
unnamed: C121.2, C123.1, U11.30 (VDD3_1)
VDD: C47.1, C49.2, C50.1, C51.1, C52.1, C53.1, C64.1, C65.2, C66.1, C67.1, C68.1, C69.1, C80.1, C85.2, C93.1, C94.1, C121.1, C122.1, U9.31 (VDD), U10.31 (VDD), U11.31 (VDD); also elsewhere on the board
